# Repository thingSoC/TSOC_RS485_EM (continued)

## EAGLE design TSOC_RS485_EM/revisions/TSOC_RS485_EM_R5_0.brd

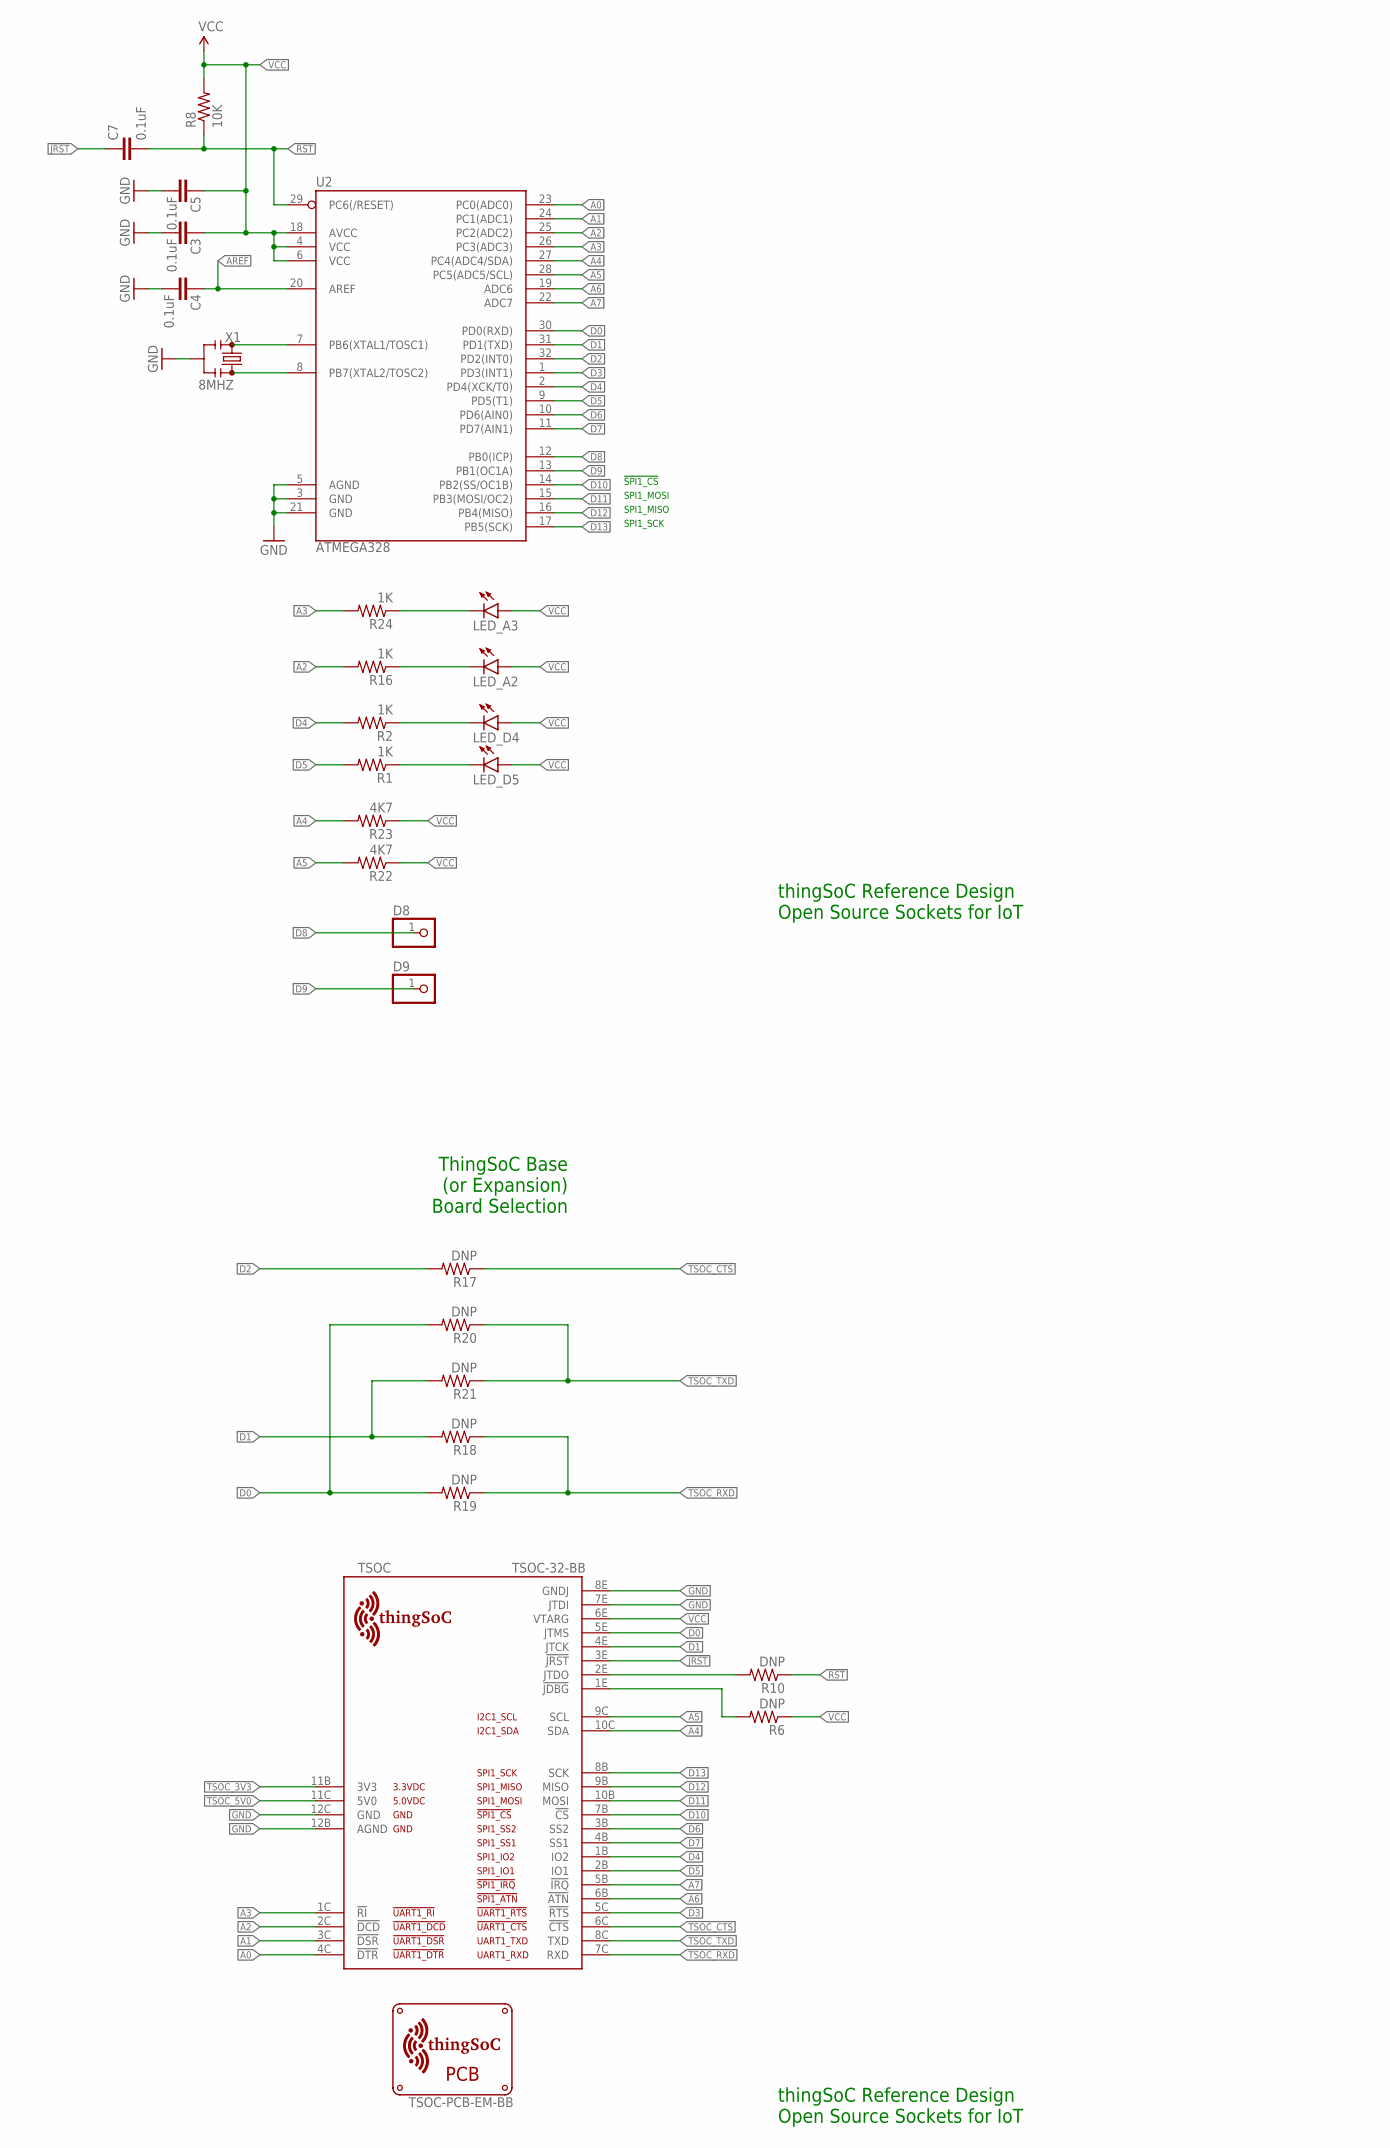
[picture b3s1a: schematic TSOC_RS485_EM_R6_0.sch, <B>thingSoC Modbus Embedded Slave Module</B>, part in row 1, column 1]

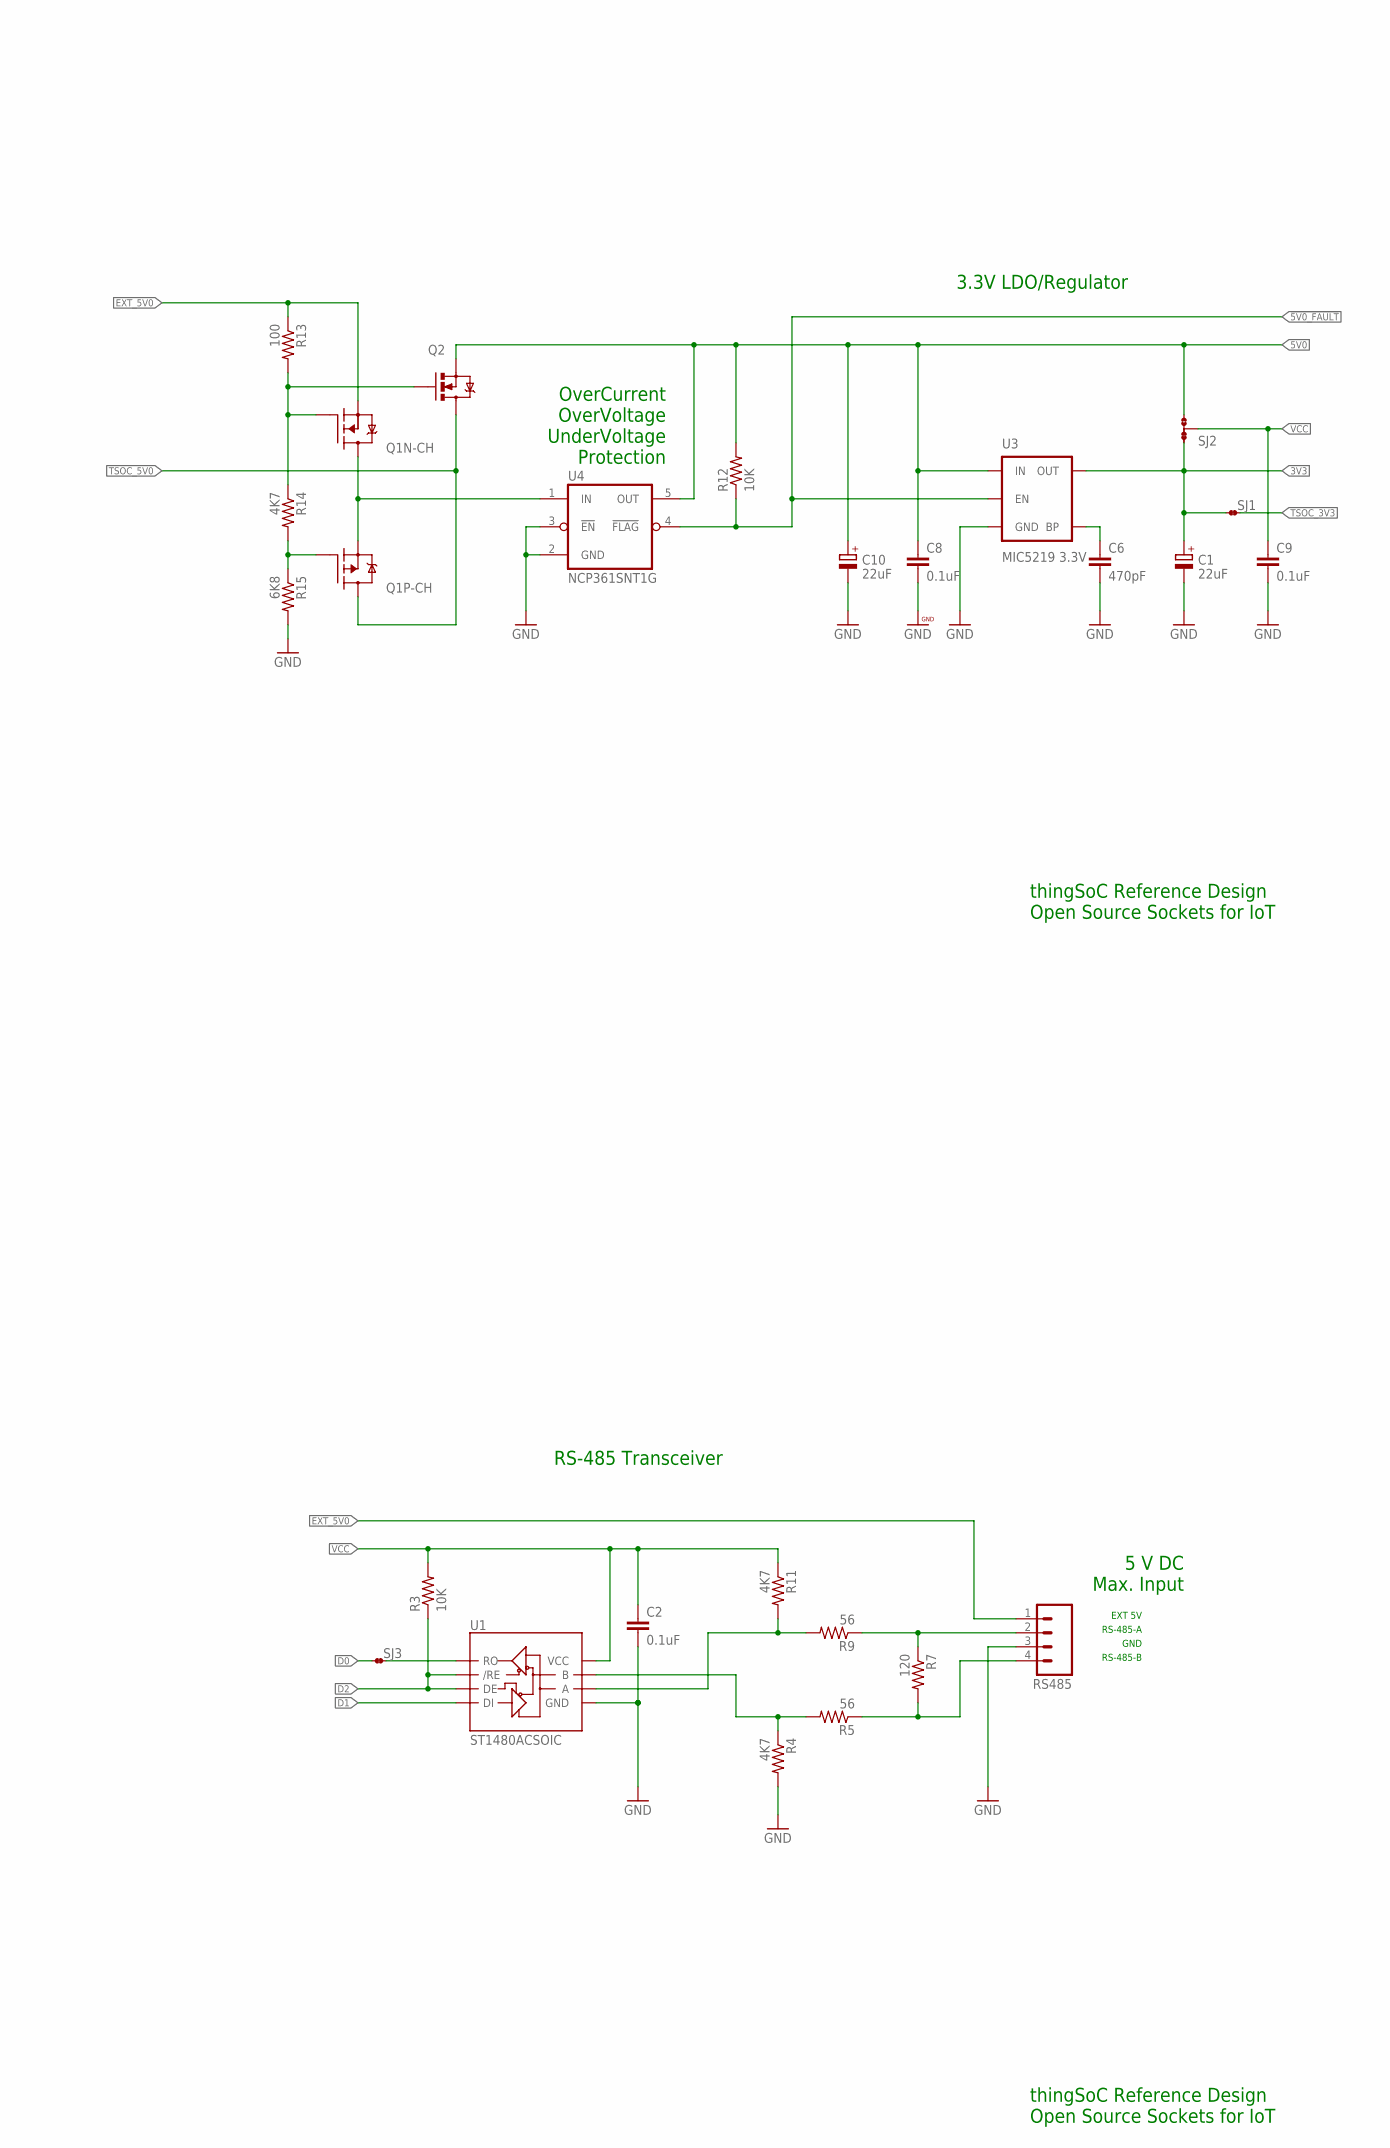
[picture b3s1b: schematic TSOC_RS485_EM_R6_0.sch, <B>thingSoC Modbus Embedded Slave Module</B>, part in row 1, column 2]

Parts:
C1, C10: 22uF; SMC_B
C2, C3, C4, C5, C7, C8, C9: 0.1uF; 0402-CAP
C6: 470pF; 0402-CAP
D8, D9: WPAD-1-0402
LED_A2, LED_A3: LED0603; LED-0603
LED_D4, LED_D5: LED0603; LED-0603
Q1: FDC6420C; SOT95P280X110-6N
Q2: MOSFET-NCHANNELAO3404A; SOT23-3
R1, R2, R16, R24: 1K; 0402-RES
R3, R8, R12: 10K; 0402-RES
R4, R11, R14, R22, R23: 4K7; 0402-RES
R5, R9: 56; 0402-RES
R6, R10, R17, R18, R19, R20, R21: DNP; 0402-RES
R7: 120; 0402-RES
R13: 100; 0402-RES
R15: 6K8; 0402-RES
RS485: M04SCREW; SCREWTERMINAL-3.5MM-4
SJ1, SJ3: JMP-2-NC
SJ2: JMP-3-1_2
TSOC: TSOC-32-BB; TSOC-BB-S32
U1: ST1480ACSOIC; SO08
U2: ATMEGA328; TQFP32-08
U3: MIC5219 3.3V; SOT23-5
U4: NCP361SNT1G; SOP95P275X110-5N
U$1: TSOC-PCB-EM-BB; TSOC-EM-BB
X1: 8MHZ; RESONATOR-SMD

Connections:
3V3: C1.+, SJ1.1, SJ2.1, U3.5 (OUT)
5V0: C8.1, C10.+, Q2.2 (S), R12.2, SJ2.3, U3.1 (IN), U4.5 (OUT)
!5V0_FAULT: R12.1, U3.3 (EN), U4.4 (!FLAG)
!JDBG: R6.2, TSOC.1E (!JDBG)
!JRST: C7.1, TSOC.3E (!JRST)
!RST: C7.2, R8.1, R10.1, U2.29 (PC6(/RESET))
A: R9.2, R11.2, U1.6 (A)
A0: TSOC.4C (!DTR), U2.23 (PC0(ADC0))
A1: TSOC.3C (!DSR), U2.24 (PC1(ADC1))
A2: R16.2, TSOC.2C (!DCD), U2.25 (PC2(ADC2))
A3: R24.2, TSOC.1C (!RI), U2.26 (PC3(ADC3))
A4: R23.2, TSOC.10C (SDA), U2.27 (PC4(ADC4/SDA))
A5: R22.2, TSOC.9C (SCL), U2.28 (PC5(ADC5/SCL))
A6: TSOC.6B (!ATN), U2.19 (ADC6)
A7: TSOC.5B (!IRQ), U2.22 (ADC7)
AO: R7.1, R9.1, RS485.2
AREF: C4.2, U2.20 (AREF)
B: R4.1, R5.2, U1.7 (B)
BO: R5.1, R7.2, RS485.4
BYPASS1: C6.1, U3.4 (BP)
D0: R19.2, R20.2, SJ3.1, TSOC.5E (JTMS), U2.30 (PD0(RXD))
D1: R18.2, R21.2, TSOC.4E (JTCK), U1.4 (DI), U2.31 (PD1(TXD))
D2: R3.1, R17.2, U1.2 (/RE), U1.3 (DE), U2.32 (PD2(INT0))
D3: TSOC.5C (!RTS), U2.1 (PD3(INT1))
D4: R2.2, TSOC.1B (IO2), U2.2 (PD4(XCK/T0))
D5: R1.2, TSOC.2B (IO1), U2.9 (PD5(T1))
D6: TSOC.3B (SS2), U2.10 (PD6(AIN0))
D7: TSOC.4B (SS1), U2.11 (PD7(AIN1))
D8: D8.1, U2.12 (PB0(ICP))
D9: D9.1, U2.13 (PB1(OC1A))
D10: TSOC.7B (!CS), U2.14 (PB2(SS/OC1B))
D11: TSOC.10B (MOSI), U2.15 (PB3(MOSI/OC2))
D12: TSOC.9B (MISO), U2.16 (PB4(MISO))
D13: TSOC.8B (SCK), U2.17 (PB5(SCK))
EXT_5V0: Q1.5 (S), R13.1, RS485.1
GND: C1.-, C2.2, C3.1, C4.1, C5.1, C6.2, C8.2, C9.2, C10.-, R4.2, R15.2, RS485.3, TSOC.7E (JTDI), TSOC.8E (GNDJ), TSOC.12B (AGND), TSOC.12C (GND), U1.5 (GND), U2.3 (GND), U2.5 (AGND), U2.21 (GND), U3.2 (GND), U4.2 (GND), U4.3 (!EN), X1.2
JTDO: R10.2, TSOC.2E (JTDO)
LEDB: LED_D4.C, R2.1
LEDG: LED_A2.C, R16.1
LEDR: LED_A3.C, R24.1
LEDY: LED_D5.C, R1.1
NGATE: Q1.1 (G), Q2.1 (G), R13.2, R14.1
PGATE: Q1.3 (G), R14.2, R15.1
RXD: SJ3.2, U1.1 (RO)
TSOC_3V3: SJ1.2, TSOC.11B (3V3)
TSOC_5V0: Q1.4 (D), Q2.3 (D), TSOC.11C (5V0)
TSOC_CTS: R17.1, TSOC.6C (!CTS)
TSOC_RXD: R18.1, R19.1, TSOC.7C (RXD)
TSOC_TXD: R20.1, R21.1, TSOC.8C (TXD)
VCC: C2.1, C3.2, C5.2, C9.1, LED_A2.A, LED_A3.A, LED_D4.A, LED_D5.A, R3.2, R6.1, R8.2, R11.1, R22.1, R23.1, SJ2.2, TSOC.6E (VTARG), U1.8 (VCC), U2.4 (VCC), U2.6 (VCC), U2.18 (AVCC)
VIN: Q1.2 (S), Q1.6 (D), U4.1 (IN)
XIN: U2.7 (PB6(XTAL1/TOSC1)), X1.3
XOUT: U2.8 (PB7(XTAL2/TOSC2)), X1.1

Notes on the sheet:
SPI1_SCK
SPI1_MISO
SPI1_MOSI
!SPI1_CS
5 V DC Max. Input
OverCurrent OverVoltage UnderVoltage Protection
3.3V LDO/Regulator
RS-485 Transceiver
EXT 5V
GND
RS-485-A
RS-485-B
ThingSoC Base (or Expansion) Board Selection
thingSoC Reference Design Open Source Sockets for IoT

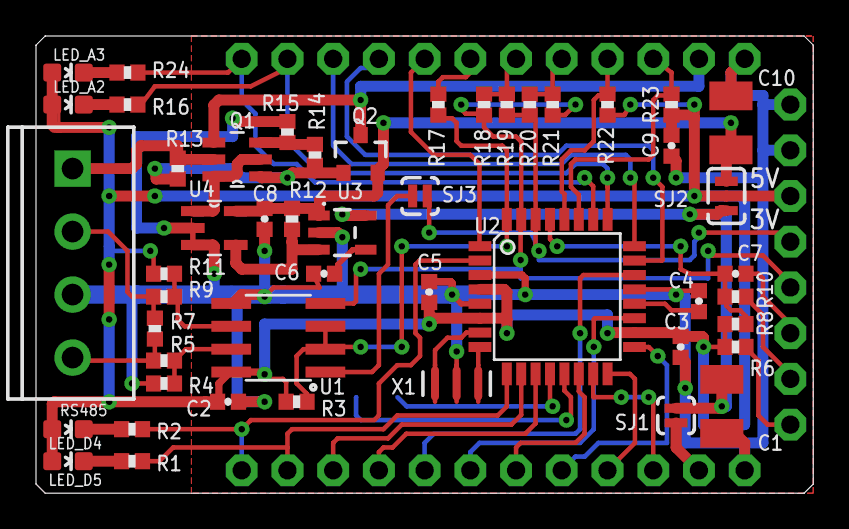
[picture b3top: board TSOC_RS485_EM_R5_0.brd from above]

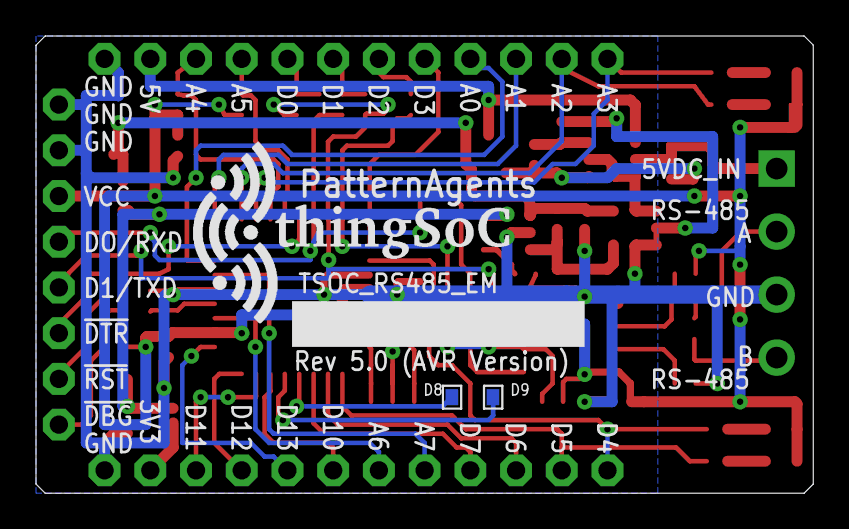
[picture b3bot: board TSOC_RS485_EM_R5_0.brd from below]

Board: 2 copper layers, 43.2 x 25.4 mm, 54 parts (3 on the bottom side), 53 nets.

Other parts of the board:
U$100: TSOC-LOGO-LRG

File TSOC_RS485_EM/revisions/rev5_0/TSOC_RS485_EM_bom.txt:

Partlist exported from /home/moxon/github/TSOC_RS485_EM/TSOC_RS485_EM/revisions/TSOC_RS485_EM_R5_0.sch at 3/14/16 5:49 PM

Qty Value                  Device                 Package               Parts                            Description                                            
1   Red                    LED0603                LED-0603              LED_A2                           Red
1   Green                  LED0603                LED-0603              LED_A3                           Greeen
1   Blue                   LED0603                LED-0603              LED_D4                           Blue
1   Yellow                 LED0603                LED-0603              LED_D5                           Yellow                                                   
1   SCREWTERMINAL          TE 1776275-4           3.5MM-4               RS485                            Header 4 Pin Screw Terminal                                                                                     
7   0.1uF                  CAP0402-CAP            0402-CAP              C2, C3, C4, C5, C7, C8, C9       Capacitor                                              
3   10K                    RESISTOR0402           0402-RES              R3, R8, R12                      Resistor                                               
1   120                    RESISTOR0402           0402-RES              R7                               Resistor                                               
4   1K                     RESISTOR0402           0402-RES              R1, R2, R16, R24                 Resistor                                               
2   22uF                   1206                   SMC_B                 C1, C10                          Capacitor                   
1   470pF                  CAP0402-CAP            0402-CAP              C6                               Capacitor                                              
5   4K7                    RESISTOR0402           0402-RES              R4, R11, R14, R22, R23           Resistor                                               
3   56                     RESISTOR0402           0402-RES              R5, R9, R13                      Resistor                                               
1   6K8                    RESISTOR0402           0402-RES              R15                              Resistor                                               
1   16MHZ                  CSTCE16M0V53-R0        RESONATOR-SMD         X1                               Resonator                                              
1   ATMEGA328P             ATMEGA328P             TQFP32-08             U2                               Atmel AVR (Arduino Compatible, Optiboot loaded)                                                       
1   FDC6420C               FDC6420C               SOT95P280X110-6N      Q1                               N and P Channel Power Trench MOSFETs                              
1   MIC5219 3.3V           V_REG_MIC52193.3V      SOT23-5               U3                               V_REG MIC5219                                          
1   MOSFET-NCHANNELAO3404A MOSFET-NCHANNELAO3404A SOT23-3               Q2                               Common NMOSFET Parts                                   
1   NCP361SNT1G            NCP361SNT1G            SOP95P275X110-5N      U4                               USB Positive Overvoltage Protection Controller         
1   ST1480ACSOIC           ST1480ACSOIC           SO08                  U1                               ST Microelectronics ST1480AC RS-485/RS-422 Transceiver 
1   TSOC-8-SERPROG         TSOC-8-SERPROG         TSOC-8-SERPROG        SERPROG                          thingSoC eight (8) Pin programming header                                  
7   DNP                    RESISTOR0402           0402-RES              R6, R10, R17, R18, R19, R20, R21 Resistor (Do Not Pupulate for Default Version)

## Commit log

2016-02-19 project update
2016-03-06 update user docs
2016-03-19 update UserGuide
2016-03-22 update BOM
2016-07-07 update to V7_0
2016-08-08 add product images
